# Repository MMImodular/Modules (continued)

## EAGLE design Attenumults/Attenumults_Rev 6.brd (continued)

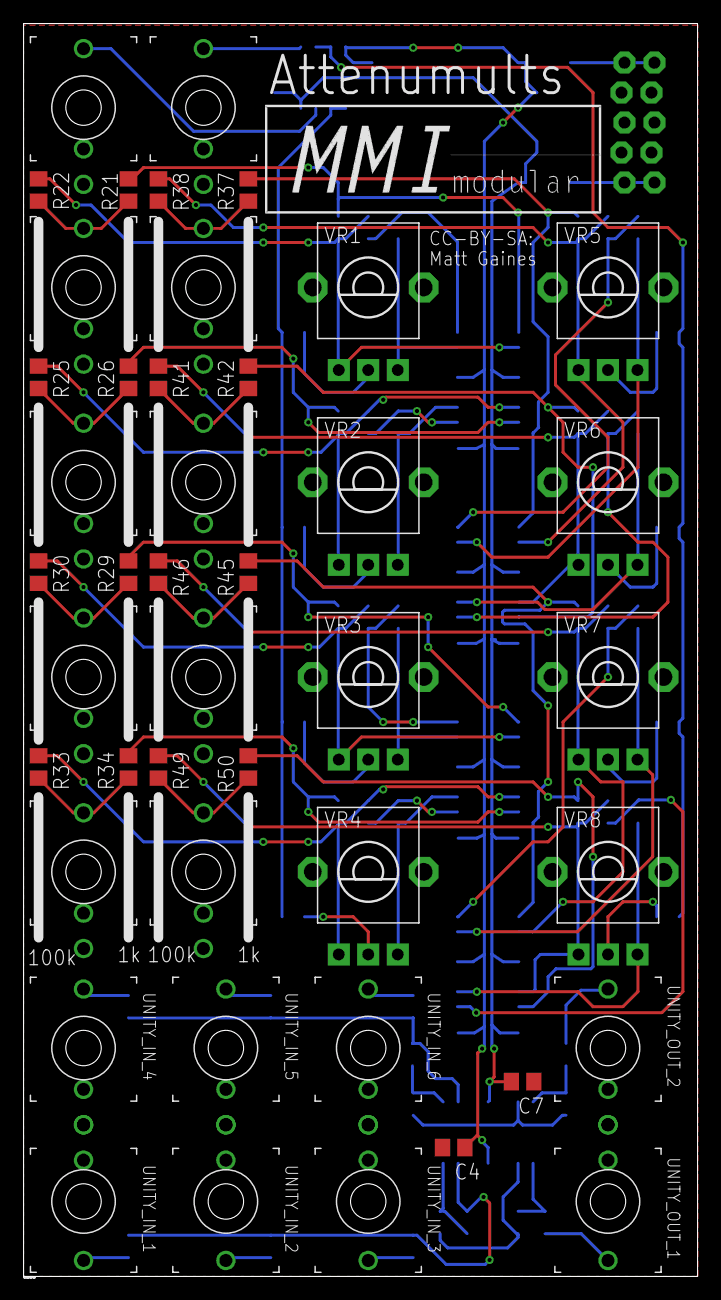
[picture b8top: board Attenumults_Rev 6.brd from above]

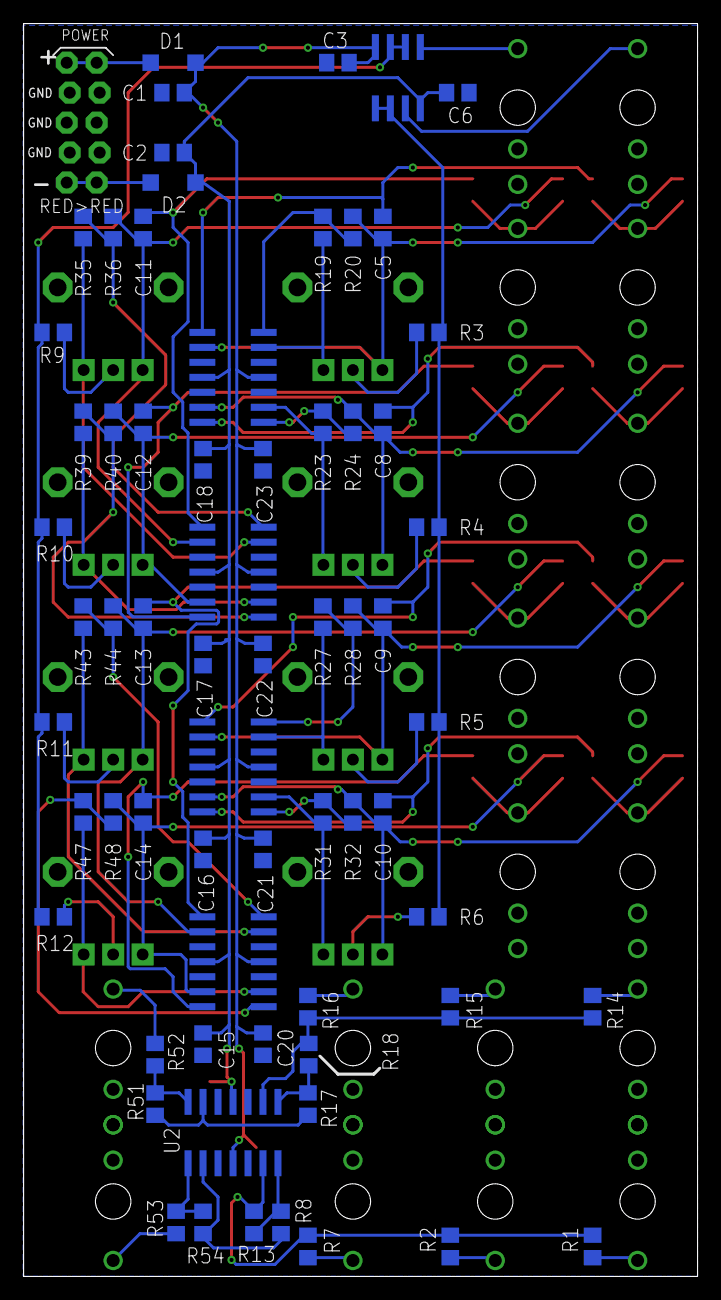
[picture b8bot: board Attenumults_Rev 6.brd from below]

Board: 2 copper layers, 57.1 x 106.2 mm, 111 parts (67 on the bottom side), 73 nets.

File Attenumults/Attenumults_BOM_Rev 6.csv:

Partlist exported from C:/Users/gaine/OneDrive/Documents/eagle/BuffAttMult/BAM_Rev 6.sch at 2/28/2018 5:56 PM

Qty Value           Device            Package              Parts                                                                                                                                                                                                             Description                              
12  .1uF            C-USC0805         C0805                C3, C4, C6, C7, C15, C16, C17, C18, C20, C21, C22, C23                                                                                                                                                            CAPACITOR, American symbol               
44  100k            R-US_R0805        R0805                R1, R2, R3, R4, R5, R6, R7, R8, R9, R10, R11, R12, R13, R14, R15, R16, R17, R18, R19, R20, R22, R23, R24, R25, R27, R28, R30, R31, R32, R33, R35, R36, R38, R39, R40, R41, R43, R44, R46, R47, R48, R49, R51, R54 RESISTOR, American symbol                
8   10k B           POT_USVERTICAL_PS ALPS_POT_VERTICAL_PS VR1, VR2, VR3, VR4, VR5, VR6, VR7, VR8                                                                                                                                                                                                                     
2   1N5819HW        DIODE-SOD123      SOD123               D1, D2                                                                                                                                                                                                            DIODE                                    
10  1k              R-US_R0805        R0805                R21, R26, R29, R34, R37, R42, R45, R50, R52, R53                                                                                                                                                                  RESISTOR, American symbol                
2   1uF             C-USC0805         C0805                C1, C2                                                                                                                                                                                                            CAPACITOR, American symbol               
8   22p             C-USC0805         C0805                C5, C8, C9, C10, C11, C12, C13, C14                                                                                                                                                                               CAPACITOR, American symbol               
1   EURO_POWER_LOCK EURO_POWER_LOCK   EURO_PWR_HEADER_LOCK U$1                                                                                                                                                                                                                                                        
18  THONKICONNNEW   THONKICONNNEW     WQP-PJ301M-12_JACK   IN_1, IN_2, OUT_1A, OUT_1B, OUT_1C, OUT_1D, OUT_2A, OUT_2B, OUT_2C, OUT_2D, UNITY_IN_1, UNITY_IN_2, UNITY_IN_3, UNITY_IN_4, UNITY_IN_5, UNITY_IN_6, UNITY_OUT_1, UNITY_OUT_2                                      3.5mm socket for Eurorack modular synths 
1   TL072           TL072_SMD         SO08                 U1                                                                                                                                                                                                                Generic Dual Op Amp                      
5   TL074           TL074_SMD         SO14                 U2, U4, U5, U6, U7                                                                                                                                                                                                Generic Quad Op Amp

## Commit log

2018-03-12 Upload Attenumults Rev 6
2018-03-12 Upload USBPower
2018-03-12 Upload product images
2018-03-12 Update Images to PNG
2018-04-17 Add Planks - Dual Precision Adder
    Not in production yet. Still needs a panel design
2018-04-17 Add Planks - Dual Precision Adder
    Not in production yet, still needs panel design.
2018-05-14 Change Gerber to Elecrow standard
2018-05-14 Remove old Gerber
2018-08-02 Fixed a woopsie
2018-08-09 Fix BOM
2018-08-18 Add schematic image and PDF version of BOM
2018-08-18 Add schematic image and PDF BOM
2018-08-18 Change BOM to xlsx, add schematic image and PDF BOM
2018-08-18 Add BOM as xlsx and pdf, add schematic as pdf
2018-09-23 Update pcb silkscreen
2018-09-23 Add Gerber
2018-09-24 Update BOM
2018-09-28 Add placement diagram
2018-09-28 Add Top Placement Diagram
2018-09-28 Add calibration instructions
2018-10-27 Upload Eagle files
2019-01-18 Update tuning procedure
2021-06-27 fixed image
